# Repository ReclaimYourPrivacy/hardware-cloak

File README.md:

hardware-cloak
==============

This is the "motherboard" for the Cloak device.

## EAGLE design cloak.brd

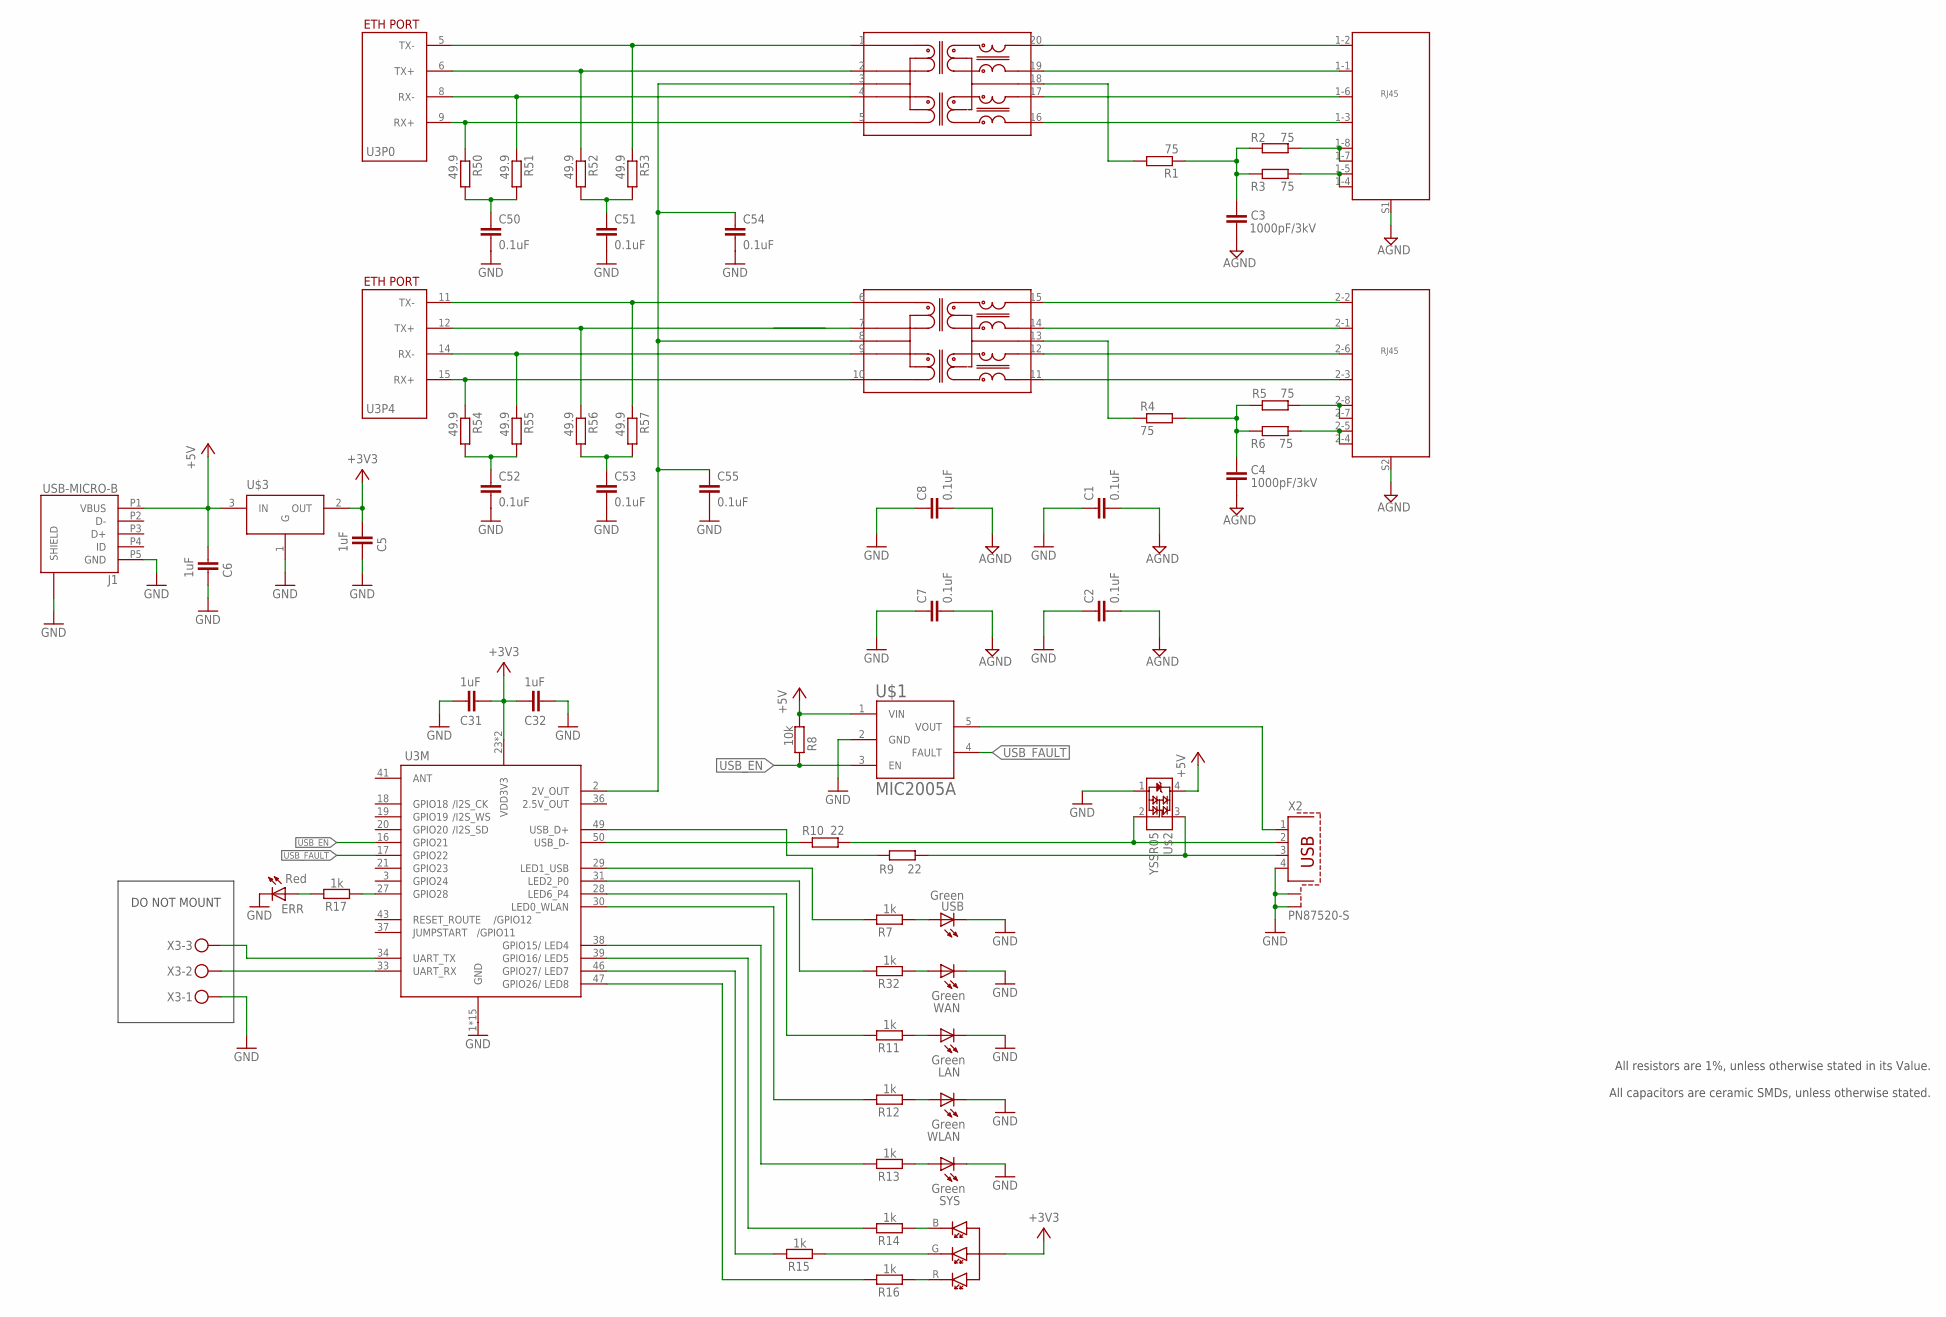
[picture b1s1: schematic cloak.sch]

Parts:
C1, C2, C7, C8: 0.1uF; C0603; PARTNO C0603C104K5RAC7411; DIGIKEY C0603C104K5RAC7411
C3, C4: 1000pF/3kV; C1808; PARTNO C1808C102KHRACTU; DIGIKEY 399-7246-2-ND
C5, C6, C31, C32: 1uF; C0603; MPN C0603C105K8PACTU; DIGIKEY 399-3118-2-ND
C50, C51, C52, C53, C54, C55: 0.1uF; C0603; MPN C0603C104K5RAC7411; DIGIKEY 399-7374-2-ND
CLOAK: LTST-C19FD1WT; MPN LTST-C19FD1WT; DIGIKEY 160-2022-2-ND
ERR: Red; CHIP-LED0603; MPN LG Q971-KN-1; DIGIKEY 475-1410-2-ND
J1: USB-MICRO-B; CON2_USB_MICRO_B_AT
LAN: Green; CHIP-LED0603; MPN LG Q971-KN-1; DIGIKEY 475-1410-2-ND
P4: ETHERNET_2PORT; SJA-1X2
R1, R2, R3, R4, R5, R6: 75; R0805; PARTNO CRCW060375R0FKEA; DIGIKEY 541-75.0HTR-ND
R7, R11, R12, R13, R14, R15, R16, R17, R32: 1k; R0603; MPN CRCW06031K0JNEA; DIGIKEY 541-1KGTR-ND
R8: 10k; R0603
R9, R10: 22; R0805; PARTNO CRCW060322R0FKEA; DIGIKEY 541-22.0HTR-ND
R50, R51, R52, R53, R54, R55, R56, R57: 49.9; R0805; MPN CRCW060349R9FKEA; DIGIKEY 541-49.9HTR-ND
SYS: Green; CHIP-LED0603; MPN LG Q971-KN-1; DIGIKEY 475-1410-2-ND
TR1: HST2038DR; H2038
U3: DRAGINO_HE
U$1: MIC2005A; SOT-23-5
U$2: YSSR05
U$3: LDO_REGL; SOT23; MPN AP2120N-3.3TRG1; DIGIKEY AP2120N-3.3TRG1DITR-ND
USB: Green; CHIP-LED0603; MPN LG Q971-KN-1; DIGIKEY 475-1410-2-ND
WAN: Green; CHIP-LED0603; MPN LG Q971-KN-1; DIGIKEY 475-1410-2-ND
WLAN: Green; CHIP-LED0603; MPN LG Q971-KN-1; DIGIKEY 475-1410-2-ND
X2: PN87520-S
X3: MKDSN1,5/3-5,08

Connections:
2.5V_OUT: U3.36 (2.5V_OUT)
2V: C54.1, C55.1, TR1.3 (CT1), TR1.8 (CT1), U3.2 (2V_OUT)
+3V3: C5.1, C31.1, C32.1, CLOAK.A, U3.23 (VDD3V3), U3.24 (VDD3V3), U$3.2 (OUT)
+5V: C6.1, J1.P1 (VBUS), R8.2, U$1.1 (VIN), U$2.4 (+), U$3.3 (IN)
AGND: C1.2, C2.2, C3.2, C4.2, C7.2, C8.2, P4.S1 (SHIELD), P4.S2 (SHIELD)
GND: C1.1, C2.1, C5.2, C6.2, C7.1, C8.1, C31.2, C32.2, C50.2, C51.2, C52.2, C53.2, C54.2, C55.2, ERR.C, J1.P5 (GND), J1.S1 (SHIELD), J1.S2 (SHIELD), J1.S3 (SHIELD), J1.S4 (SHIELD), J1.S5 (SHIELD), J1.S6 (SHIELD), LAN.C, SYS.C, U3.1 (GND), U3.4 (GND), U3.7 (GND), U3.10 (GND), U3.13 (GND), U3.22 (GND), U3.25 (GND), U3.26 (GND), U3.32 (GND), U3.35 (GND), U3.40 (GND), U3.42 (GND), U3.44 (GND), U3.45 (GND), U3.48 (GND), U$1.2 (GND), U$2.1 (C), U$3.1 (G), USB.C, WAN.C, WLAN.C, X2.4, X2.S1, X2.S2, X3.1
unnamed: R32.2, WAN.A
unnamed: R7.2, USB.A
unnamed: U$1.5 (VOUT), X2.1
unnamed: R10.2, U3.50 (USB_D-)
unnamed: R9.2, U3.49 (USB_D+)
unnamed: R10.1, U$2.2 (B), X2.2
unnamed: R9.1, U$2.3 (A), X2.3
unnamed: LAN.A, R11.2
unnamed: R12.2, WLAN.A
unnamed: R13.2, SYS.A
unnamed: CLOAK.B, R14.2
unnamed: R7.1, U3.29 (LED1_USB)
unnamed: R32.1, U3.31 (LED2_P0)
unnamed: R11.1, U3.28 (LED6_P4)
unnamed: R12.1, U3.30 (LED0_WLAN)
unnamed: R13.1, U3.38 (LED4)
unnamed: R14.1, U3.39 (LED5)
unnamed: CLOAK.G, R15.2
unnamed: CLOAK.R, R16.2
unnamed: R15.1, U3.46 (LED7)
unnamed: R16.1, U3.47 (LED8)
unnamed: ERR.A, R17.1
unnamed: C50.1, R50.2, R51.2
unnamed: R17.2, U3.27 (GPIO28)
unnamed: C51.1, R52.2, R53.2
unnamed: C52.1, R54.2, R55.2
unnamed: C53.1, R56.2, R57.2
unnamed: P4.1-2 (2), TR1.20 (TX+)
unnamed: P4.1-1 (1), TR1.19 (TX-)
unnamed: P4.1-6 (6), TR1.17 (RX+)
unnamed: P4.1-3 (3), TR1.16 (RX-)
unnamed: P4.1-7 (7), P4.1-8 (8), R2.1
unnamed: P4.1-4 (4), P4.1-5 (5), R3.1
unnamed: P4.2-7 (7), P4.2-8 (8), R5.1
unnamed: P4.2-4 (4), P4.2-5 (5), R6.2
unnamed: C4.1, R4.2, R5.2, R6.1
unnamed: C3.1, R1.1, R2.2, R3.2
unnamed: P4.2-2 (2), TR1.15 (TX+)
unnamed: P4.2-1 (1), TR1.14 (TX-)
unnamed: P4.2-6 (6), TR1.12 (RX+)
unnamed: P4.2-3 (3), TR1.11 (RX-)
unnamed: R4.1, TR1.13 (CT2)
unnamed: R1.2, TR1.18 (CT2)
P0-RX+: R50.1, TR1.5 (RD-), U3.9 (RX+)
P0-RX-: R51.1, TR1.4 (RD+), U3.8 (RX-)
P0-TX+: R52.1, TR1.2 (TD-), U3.6 (TX+)
P0-TX-: R53.1, TR1.1 (TD+), U3.5 (TX-)
P4-RX+: R54.1, TR1.10 (RD-), U3.15 (RX+)
P4-RX-: R55.1, TR1.9 (RD+), U3.14 (RX-)
P4-TX+: R56.1, TR1.7 (TD-), U3.12 (TX+)
P4-TX-: R57.1, TR1.6 (TD+), U3.11 (TX-)
RX: U3.33 (UART_RX), X3.2
TX: U3.34 (UART_TX), X3.3
USB_EN: R8.1, U3.16 (GPIO21), U$1.3 (EN)
USB_FAULT: U3.17 (GPIO22), U$1.4 (FAULT)

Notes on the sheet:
All resistors are 1%, unless otherwise stated in its Value. All capacitors are ceramic SMDs, unless otherwise stated.
DO NOT MOUNT

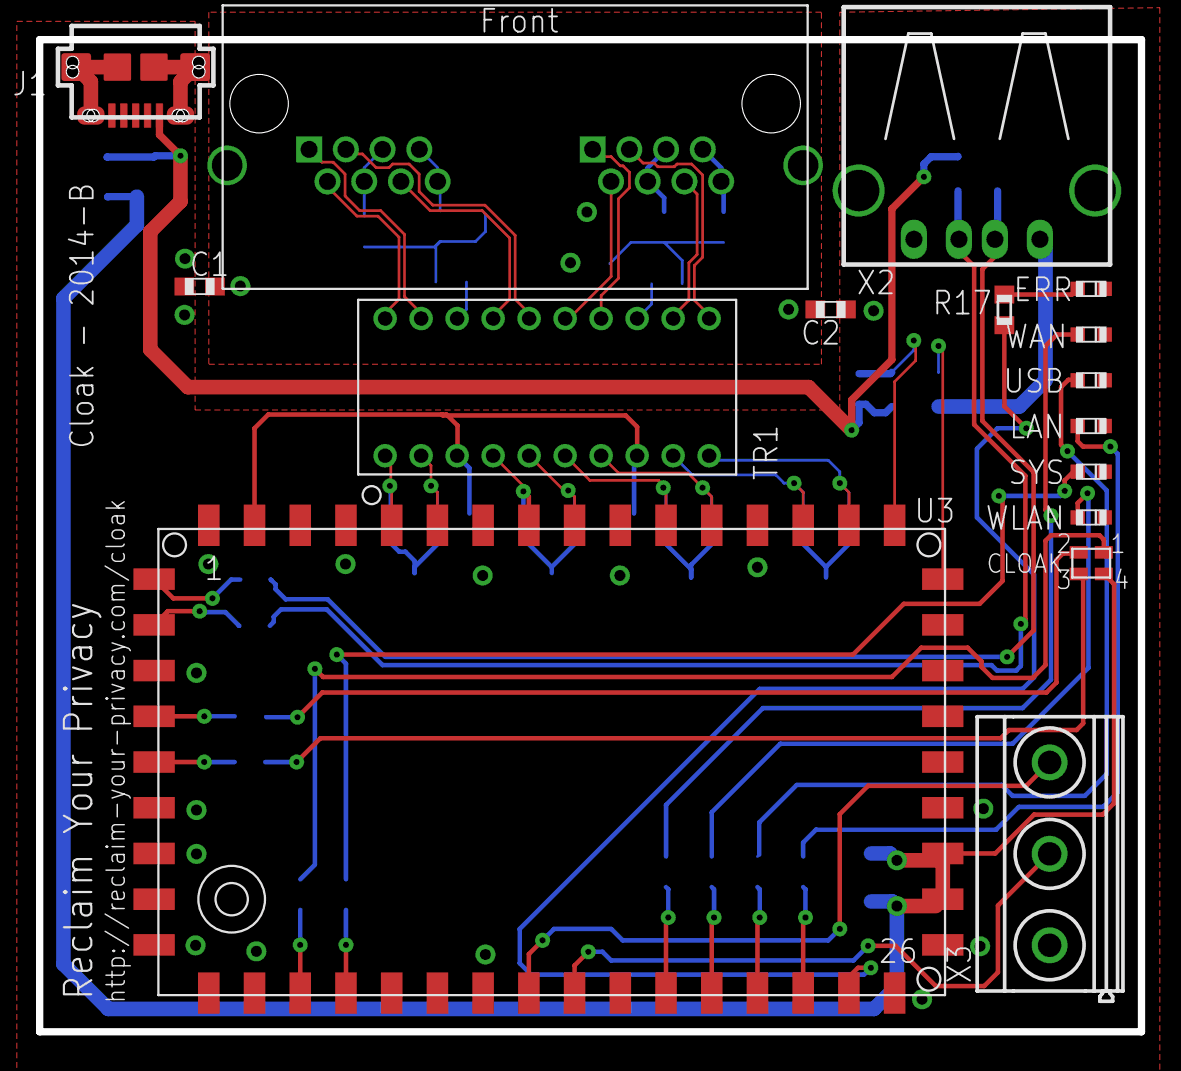
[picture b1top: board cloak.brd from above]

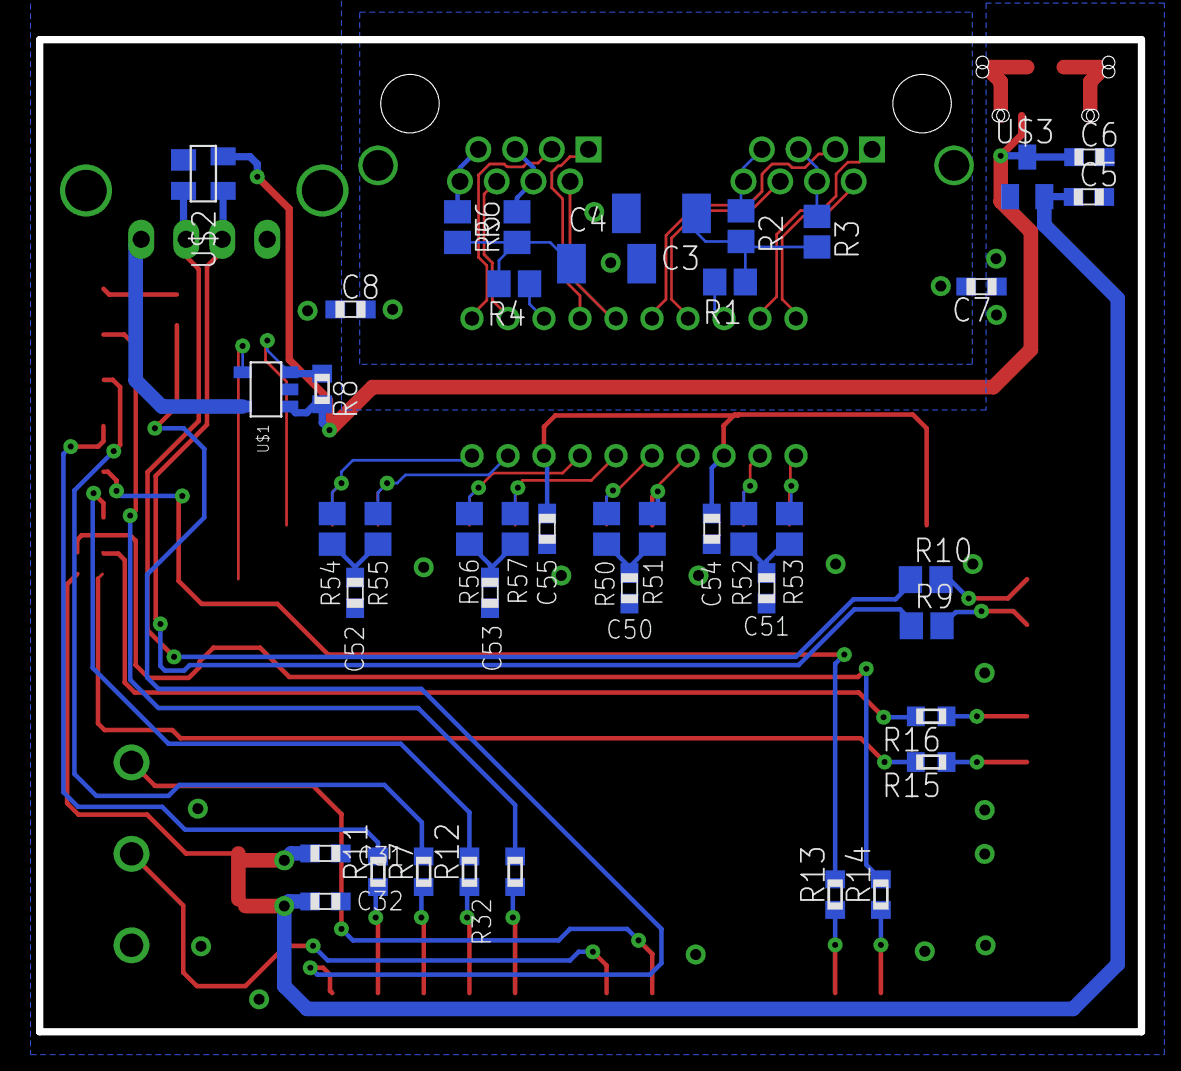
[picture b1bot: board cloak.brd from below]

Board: 2 copper layers, 61.2 x 55.1 mm, 58 parts (42 on the bottom side), 60 nets.

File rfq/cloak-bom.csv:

"Part";"Value";"Device";"Package";"Description";"DIGIKEY";"DIGIKEY_LOW";"MANUFACTURER";"MF";"MPN";"OC_FARNELL";"OC_NEWARK";"PARTNO";"SUPPLIER";"VALUE";
"C1";"0.1uF";"C-EUC0603";"C0603";"CAPACITOR, European symbol";"C0603C104K5RAC7411";"";"Kemet";"";"";"";"";"C0603C104K5RAC7411";"";"";
"C2";"0.1uF";"C-EUC0603";"C0603";"CAPACITOR, European symbol";"C0603C104K5RAC7411";"";"Kemet";"";"";"";"";"C0603C104K5RAC7411";"";"";
"C3";"1000pF/3kV";"C-EUC1808";"C1808";"CAPACITOR, European symbol";"399-7246-2-ND";"399-7246-6-ND";"Kemet";"";"";"";"";"C1808C102KHRACTU";"";"";
"C4";"1000pF/3kV";"C-EUC1808";"C1808";"CAPACITOR, European symbol";"399-7246-2-ND";"399-7246-6-ND";"Kemet";"";"";"";"";"C1808C102KHRACTU";"";"";
"C5";"1uF";"C-EUC0603";"C0603";"CAPACITOR, European symbol";"399-3118-2-ND";"399-3118-6-ND";"";"Kemet";"C0603C105K8PACTU";"";"";"";"";"";
"C6";"1uF";"C-EUC0603";"C0603";"CAPACITOR, European symbol";"399-3118-2-ND";"399-3118-6-ND";"";"Kemet";"C0603C105K8PACTU";"";"";"";"";"";
"C7";"0.1uF";"C-EUC0603";"C0603";"CAPACITOR, European symbol";"C0603C104K5RAC7411";"";"Kemet";"";"";"";"";"C0603C104K5RAC7411";"";"";
"C8";"0.1uF";"C-EUC0603";"C0603";"CAPACITOR, European symbol";"C0603C104K5RAC7411";"";"Kemet";"";"";"";"";"C0603C104K5RAC7411";"";"";
"C31";"1uF";"C-EUC0603";"C0603";"CAPACITOR, European symbol";"399-3118-2-ND";"399-3118-6-ND";"";"Kemet";"C0603C105K8PACTU";"";"";"";"";"";
"C32";"1uF";"C-EUC0603";"C0603";"CAPACITOR, European symbol";"399-3118-2-ND";"399-3118-6-ND";"";"Kemet";"C0603C105K8PACTU";"";"";"";"";"";
"C50";"0.1uF";"C-EUC0603";"C0603";"CAPACITOR, European symbol";"399-7374-2-ND";"";"";"Kemet";"C0603C104K5RAC7411";"";"";"";"";"";
"C51";"0.1uF";"C-EUC0603";"C0603";"CAPACITOR, European symbol";"399-7374-2-ND";"";"";"Kemet";"C0603C104K5RAC7411";"";"";"";"";"";
"C52";"0.1uF";"C-EUC0603";"C0603";"CAPACITOR, European symbol";"399-7374-2-ND";"";"";"Kemet";"C0603C104K5RAC7411";"";"";"";"";"";
"C53";"0.1uF";"C-EUC0603";"C0603";"CAPACITOR, European symbol";"399-7374-2-ND";"";"";"Kemet";"C0603C104K5RAC7411";"";"";"";"";"";
"C54";"0.1uF";"C-EUC0603";"C0603";"CAPACITOR, European symbol";"399-7374-2-ND";"";"";"Kemet";"C0603C104K5RAC7411";"";"";"";"";"";
"C55";"0.1uF";"C-EUC0603";"C0603";"CAPACITOR, European symbol";"399-7374-2-ND";"";"";"Kemet";"C0603C104K5RAC7411";"";"";"";"";"";
"CLOAK";"LTST-C19FD1WT";"LTST-C19FD1WT";"LTST-C19FD1WT";"";"160-2022-2-ND";"";"";"Lite-On Inc";"LTST-C19FD1WT";"";"";"";"";"";
"ERR";"Red";"LEDCHIP-LED0603";"CHIP-LED0603";"LED";"475-1410-2-ND";"475-1409-6-ND";"";"OSRAM Opto Semiconductors Inc";"LG Q971-KN-1";"";"";"";"";"";
"J1";"USB-MICRO-B";"USB-MICRO-B";"CON2_USB_MICRO_B_AT";"";"";"";"";"";"";"";"";"";"";"";
"LAN";"Green";"LEDCHIP-LED0603";"CHIP-LED0603";"LED";"475-1410-2-ND";"475-1409-6-ND";"";"OSRAM Opto Semiconductors Inc";"LG Q971-KN-1";"";"";"";"";"";
"P4";"ETHERNET_2PORT";"ETHERNET_2PORT";"SJA-1X2";"";"";"";"";"";"";"";"";"";"";"";
"R1";"75";"R-EU_R0805";"R0805";"RESISTOR, European symbol";"541-75.0HTR-ND";"541-75.0HDKR-ND";"Vishay Dale";"";"";"";"";"CRCW060375R0FKEA";"";"";
"R2";"75";"R-EU_R0805";"R0805";"RESISTOR, European symbol";"541-75.0HTR-ND";"541-75.0HDKR-ND";"Vishay Dale";"";"";"";"";"CRCW060375R0FKEA";"";"";
"R3";"75";"R-EU_R0805";"R0805";"RESISTOR, European symbol";"541-75.0HTR-ND";"541-75.0HDKR-ND";"Vishay Dale";"";"";"";"";"CRCW060375R0FKEA";"";"";
"R4";"75";"R-EU_R0805";"R0805";"RESISTOR, European symbol";"541-75.0HTR-ND";"541-75.0HDKR-ND";"Vishay Dale";"";"";"";"";"CRCW060375R0FKEA";"";"";
"R5";"75";"R-EU_R0805";"R0805";"RESISTOR, European symbol";"541-75.0HTR-ND";"541-75.0HDKR-ND";"Vishay Dale";"";"";"";"";"CRCW060375R0FKEA";"";"";
"R6";"75";"R-EU_R0805";"R0805";"RESISTOR, European symbol";"541-75.0HTR-ND";"541-75.0HDKR-ND";"Vishay Dale";"";"";"";"";"CRCW060375R0FKEA";"";"";
"R7";"1k";"R-EU_R0603";"R0603";"RESISTOR, European symbol";"541-1KGTR-ND";"541-1KGDKR-ND";"";"Vishay Dale";"CRCW06031K0JNEA";"";"";"";"";"";
"R8";"10k";"R-EU_R0603";"R0603";"RESISTOR, European symbol";"";"";"";"Vishay Dale";"";"";"";"";"";"";
"R9";"22";"R-EU_R0805";"R0805";"RESISTOR, European symbol";"541-22.0HTR-ND";"541-22.0HDKR-ND";"Vishay Dale";"";"";"";"";"CRCW060322R0FKEA";"";"";
"R10";"22";"R-EU_R0805";"R0805";"RESISTOR, European symbol";"541-22.0HTR-ND";"541-22.0HDKR-ND";"Vishay Dale";"";"";"";"";"CRCW060322R0FKEA";"";"";
"R11";"1k";"R-EU_R0603";"R0603";"RESISTOR, European symbol";"541-1KGTR-ND";"541-1KGDKR-ND";"";"Vishay Dale";"CRCW06031K0JNEA";"";"";"";"";"";
"R12";"1k";"R-EU_R0603";"R0603";"RESISTOR, European symbol";"541-1KGTR-ND";"541-1KGDKR-ND";"";"Vishay Dale";"CRCW06031K0JNEA";"";"";"";"";"";
"R13";"1k";"R-EU_R0603";"R0603";"RESISTOR, European symbol";"541-1KGTR-ND";"541-1KGDKR-ND";"";"Vishay Dale";"CRCW06031K0JNEA";"";"";"";"";"";
"R14";"1k";"R-EU_R0603";"R0603";"RESISTOR, European symbol";"541-1KGTR-ND";"541-1KGDKR-ND";"";"Vishay Dale";"CRCW06031K0JNEA";"";"";"";"";"";
"R15";"1k";"R-EU_R0603";"R0603";"RESISTOR, European symbol";"541-1KGTR-ND";"541-1KGDKR-ND";"";"Vishay Dale";"CRCW06031K0JNEA";"";"";"";"";"";
"R16";"1k";"R-EU_R0603";"R0603";"RESISTOR, European symbol";"541-1KGTR-ND";"541-1KGDKR-ND";"";"Vishay Dale";"CRCW06031K0JNEA";"";"";"";"";"";
"R17";"1k";"R-EU_R0603";"R0603";"RESISTOR, European symbol";"541-1KGTR-ND";"541-1KGDKR-ND";"";"Vishay Dale";"CRCW06031K0JNEA";"";"";"";"";"";
"R32";"1k";"R-EU_R0603";"R0603";"RESISTOR, European symbol";"541-1KGTR-ND";"541-1KGDKR-ND";"";"Vishay Dale";"CRCW06031K0JNEA";"";"";"";"";"";
"R50";"49.9";"R-EU_R0805";"R0805";"RESISTOR, European symbol";"541-49.9HTR-ND";"541-49.9HDKR-ND";"";"Vishay Dale";"CRCW060349R9FKEA";"";"";"";"";"";
"R51";"49.9";"R-EU_R0805";"R0805";"RESISTOR, European symbol";"541-49.9HTR-ND";"541-49.9HDKR-ND";"";"Vishay Dale";"CRCW060349R9FKEA";"";"";"";"";"";
"R52";"49.9";"R-EU_R0805";"R0805";"RESISTOR, European symbol";"541-49.9HTR-ND";"541-49.9HDKR-ND";"";"Vishay Dale";"CRCW060349R9FKEA";"";"";"";"";"";
"R53";"49.9";"R-EU_R0805";"R0805";"RESISTOR, European symbol";"541-49.9HTR-ND";"541-49.9HDKR-ND";"";"Vishay Dale";"CRCW060349R9FKEA";"";"";"";"";"";
"R54";"49.9";"R-EU_R0805";"R0805";"RESISTOR, European symbol";"541-49.9HTR-ND";"541-49.9HDKR-ND";"";"Vishay Dale";"CRCW060349R9FKEA";"";"";"";"";"";
"R55";"49.9";"R-EU_R0805";"R0805";"RESISTOR, European symbol";"541-49.9HTR-ND";"541-49.9HDKR-ND";"";"Vishay Dale";"CRCW060349R9FKEA";"";"";"";"";"";
"R56";"49.9";"R-EU_R0805";"R0805";"RESISTOR, European symbol";"541-49.9HTR-ND";"541-49.9HDKR-ND";"";"Vishay Dale";"CRCW060349R9FKEA";"";"";"";"";"";
"R57";"49.9";"R-EU_R0805";"R0805";"RESISTOR, European symbol";"541-49.9HTR-ND";"541-49.9HDKR-ND";"";"Vishay Dale";"CRCW060349R9FKEA";"";"";"";"";"";
"SYS";"Green";"LEDCHIP-LED0603";"CHIP-LED0603";"LED";"475-1410-2-ND";"475-1409-6-ND";"";"OSRAM Opto Semiconductors Inc";"LG Q971-KN-1";"";"";"";"";"";
"TR1";"HST2038DR";"HST2038DR";"H2038";"";"";"";"";"";"";"";"";"";"Dragino";"";
"U$1";"MIC2005A";"MIC2005A";"SOT-23-5";"";"";"";"";"";"";"";"";"";"";"";
"U$2";"YSSR05";"YSSR05";"YSSR05";"High Speed Protection Diod Array";"";"";"";"";"";"";"";"";"";"YSSR05";
"U$3";"";"LDO_REGL";"SOT23";"";"AP2120N-3.3TRG1DITR-ND ";"";"";"Diodes Inc";"AP2120N-3.3TRG1";"";"";"";"";"";
"U3";"DRAGINO_HE";"DRAGINO_HE";"DRAGINO_HE";"Dragino HE Module";"";"";"";"";"";"";"";"";"";"";
"USB";"Green";"LEDCHIP-LED0603";"CHIP-LED0603";"LED";"475-1410-2-ND";"475-1409-6-ND";"";"OSRAM Opto Semiconductors Inc";"LG Q971-KN-1";"";"";"";"";"";
"WAN";"Green";"LEDCHIP-LED0603";"CHIP-LED0603";"LED";"475-1410-2-ND";"475-1409-6-ND";"";"OSRAM Opto Semiconductors Inc";"LG Q971-KN-1";"";"";"";"";"";
"WLAN";"Green";"LEDCHIP-LED0603";"CHIP-LED0603";"LED";"475-1410-2-ND";"475-1409-6-ND";"";"OSRAM Opto Semiconductors Inc";"LG Q971-KN-1";"";"";"";"";"";
"X2";"PN87520-S";"PN87520-S";"PN87520-S";"";"";"";"";"";"";"unknown";"unknown";"";"";"";
"X3";"";"MKDSN1,5/3-5,08";"MKDSN1,5/3-5,08";"MKDSN 1,5/ 3-5,08 Printklemme";"";"";"";"";"SMKDSN1,5/3-5,08";"1792904";"70R0299";"";"";"";

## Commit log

2014-10-17 First public release.
2014-10-17 Added Solderpad License to this work.
2014-10-17 Added the RFQ that went out earlier.
2014-10-21 Added 3D model.
2014-10-21 Added trafo.

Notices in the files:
parts and their libraries:
frames: (c) 2014 Bright Things Ltd, All Rights Reserved
